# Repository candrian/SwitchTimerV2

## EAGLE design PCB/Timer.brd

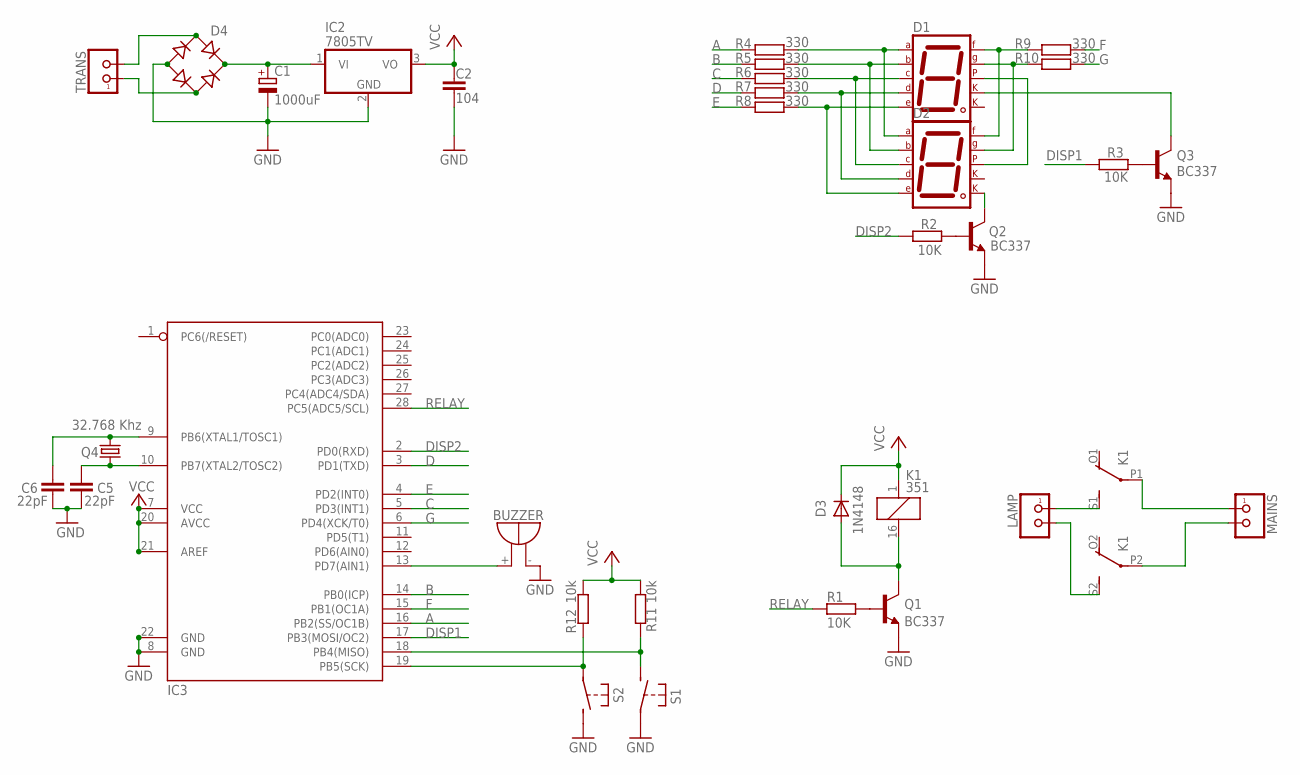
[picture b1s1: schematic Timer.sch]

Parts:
BUZZER: F/HMB
C1: 1000uF; C-TT2D13-SIDE
C2: 104; C-22X6(FAKI)
C5, C6: 22pF; C-22X6(FAKI)
D1, D2: 7SEG-CK; 7SEG-13
D3: 1N4148; DO35-10
D4: RECTIFIER-1A
IC2: 7805TV; TO220V
IC3: ATMEGA-8-P; DIL28-3
K1: 351
LAMP: KLEMESX2
MAINS: KLEMESX2
Q1, Q2, Q3: BC337; TO92-EBC
Q4: 32.768 Khz; TC38
R1, R2, R3: 10K; R0270/10
R4, R5, R6, R7, R8, R9, R10: 330; R0270/10
R11, R12: 10k; R0270/10
S1, S2: SWITCH; SW-BT
TRANS: KLEMESX2

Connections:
A: IC3.16 (PB2(SS/OC1B)), R4.1
B: IC3.14 (PB0(ICP)), R5.1
C: IC3.5 (PD3(INT1)), R6.1
D: IC3.3 (PD1(TXD)), R7.1
DISP1: IC3.17 (PB3(MOSI/OC2)), R3.2
DISP2: IC3.2 (PD0(RXD)), R2.2
E: IC3.4 (PD2(INT0)), R8.1
F: IC3.15 (PB1(OC1A)), R9.2
G: IC3.6 (PD4(XCK/T0)), R10.2
GND: BUZZER.-, C1.-, C2.2, C5.2, C6.2, D4.-, IC2.2 (GND), IC3.8 (GND), IC3.22 (GND), Q1.E, Q2.E, Q3.E, S1.P$1, S2.P$2 (S)
unnamed: D4.AC1, TRANS.2
unnamed: K1.P2, MAINS.2
unnamed: C1.+, D4.+, IC2.1 (VI)
unnamed: D1.4 (C), D2.4 (C), R6.2
unnamed: C5.1, IC3.10 (PB7(XTAL2/TOSC2)), Q4.1
unnamed: K1.P1, MAINS.1
unnamed: D1.6 (B), D2.6 (B), R5.2
unnamed: D1.7 (A), D2.7 (A), R4.2
unnamed: D1.2 (D), D2.2 (D), R7.2
unnamed: D1.1 (E), D2.1 (E), R8.2
unnamed: D1.9 (F), D2.9 (F), R9.1
unnamed: D1.5 (DP), D2.5 (DP)
unnamed: Q3.B, R3.1
unnamed: D1.10 (G), D2.10 (G), R10.1
unnamed: K1.S2 (S), LAMP.2
unnamed: C6.1, IC3.9 (PB6(XTAL1/TOSC1)), Q4.2
unnamed: Q2.B, R2.1
unnamed: D2.8 (CK2), Q2.C
unnamed: D1.3 (CK1), Q3.C
unnamed: BUZZER.+, IC3.13 (PD7(AIN1))
unnamed: IC3.19 (PB5(SCK)), R12.1, S2.P$1
unnamed: D3.A, K1.16 (2), Q1.C
unnamed: Q1.B, R1.2
unnamed: D4.AC2, TRANS.1
unnamed: IC3.18 (PB4(MISO)), R11.1, S1.P$2 (S)
unnamed: K1.S1 (S), LAMP.1
RELAY: IC3.28 (PC5(ADC5/SCL)), R1.1
VCC: C2.1, D3.C, IC2.3 (VO), IC3.7 (VCC), IC3.20 (AVCC), IC3.21 (AREF), K1.1, R11.2, R12.2

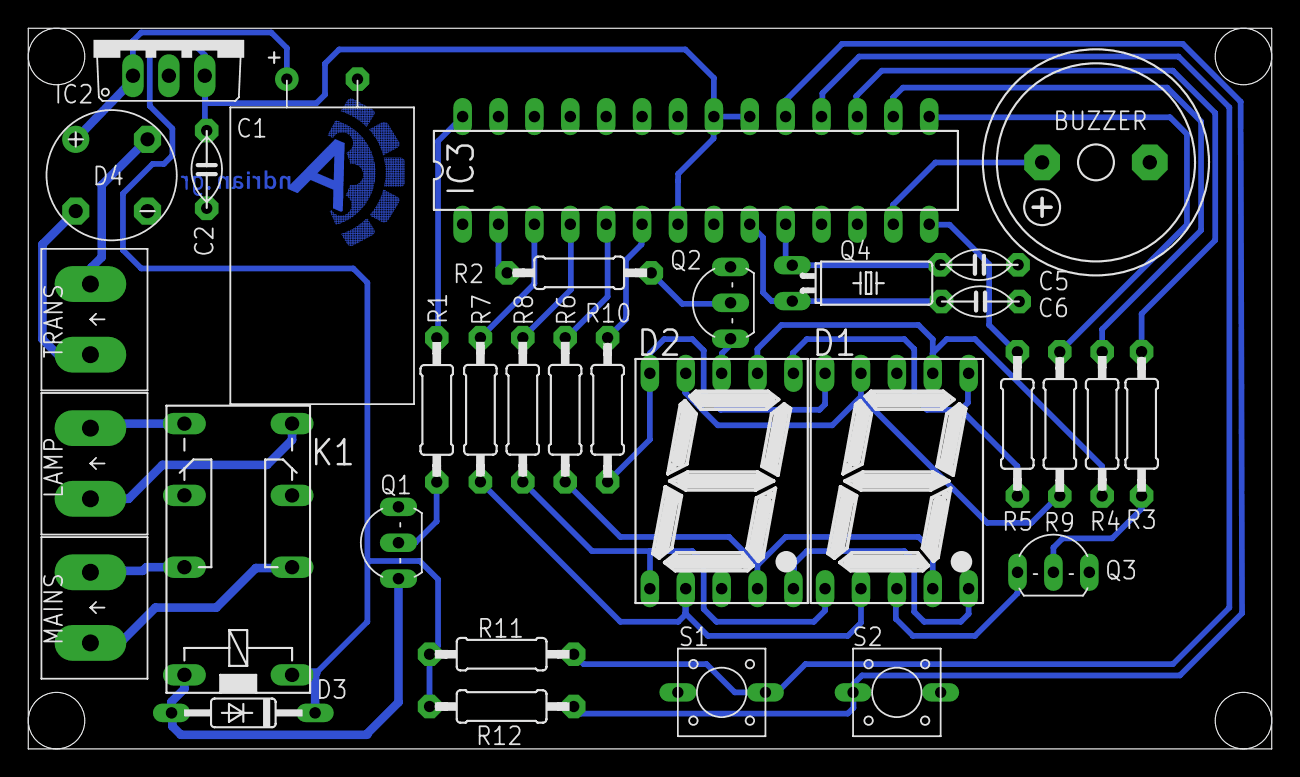
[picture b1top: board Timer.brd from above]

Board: 2 copper layers, 88.0 x 51.0 mm, 34 parts (0 on the bottom side), 38 nets.

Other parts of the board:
U$1: CANDRIAN-LOGO/SMALL/BOTTOM

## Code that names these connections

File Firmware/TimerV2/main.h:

#define DDR_RELAY   DDRC
#define DDR_BUZZER  DDRD
#define DDR_SW1     DDRB
#define DDR_SW2     DDRB
#define DDR_DISP1   DDRD
#define DDR_DISP2   DDRB
#define DDR_A       DDRB
#define DDR_B       DDRB
#define DDR_C       DDRD
#define DDR_D       DDRD
#define DDR_E       DDRD
#define DDR_F       DDRB
#define DDR_G       DDRD

#define PORT_RELAY  PORTC
#define PORT_BUZZER PORTD
#define PORT_SW1    PORTB
#define PORT_SW2    PORTB
#define PORT_DISP1  PORTD
#define PORT_DISP2  PORTB
#define PORT_A      PORTB
#define PORT_B      PORTB
#define PORT_C      PORTD
#define PORT_D      PORTD
#define PORT_E      PORTD
#define PORT_F      PORTB
#define PORT_G      PORTD

#define PIN_SW1     PINB
#define PIN_SW2     PINB

#define RELAY       PC5
#define BUZZER      PD7
#define SW1         PB4
#define SW2         PB5
#define DISP1       PD0
#define DISP2       PB3
#define A           PB2
#define B           PB0
#define C           PD3
#define D           PD1
#define E           PD2
#define F           PB1
#define G           PD4

#define DIG_0       0x7E
#define DIG_1       0x30
#define DIG_2       0x6D
#define DIG_3       0x79
#define DIG_4       0x33
#define DIG_5       0x5B
#define DIG_6       0x1F
#define DIG_7       0x70
#define DIG_8       0x7F
#define DIG_9       0x73

#define EE_LIMIT    10

#define MUX_DIVIDER (40UL)
